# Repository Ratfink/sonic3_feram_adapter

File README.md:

# sonic3_feram_adapter
Breakout/adapter board for replacing the FeRAM chip in a Sonic 3 cartridge with
a modern chip.

## Licensing
Copyright © 2016 Clayton G. Hobbs.

This work is licensed under the Creative Commons Attribution-ShareAlike 4.0
International License. To view a copy of this license, visit
http://creativecommons.org/licenses/by-sa/4.0/ or send a letter to Creative
Commons, PO Box 1866, Mountain View, CA 94042, USA.

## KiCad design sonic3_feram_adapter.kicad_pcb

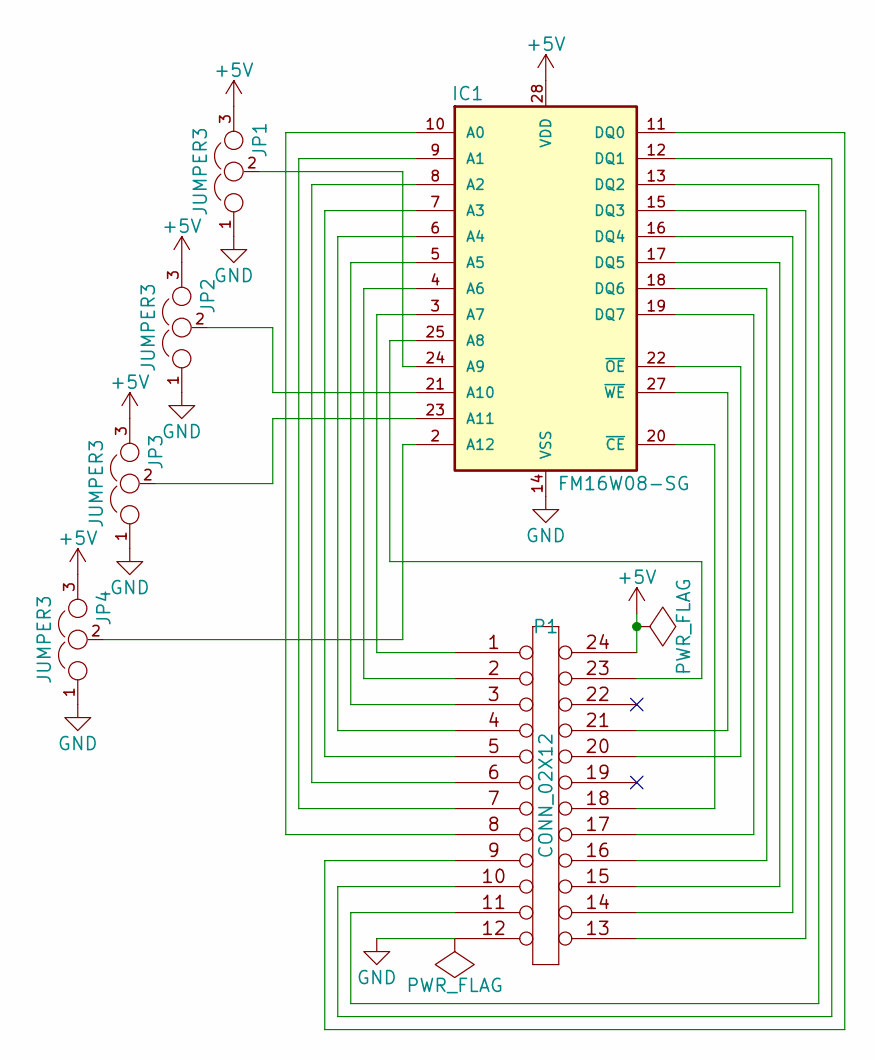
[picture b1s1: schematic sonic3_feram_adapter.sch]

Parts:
IC1: FM16W08-SG; SOIC-28_7.5x17.9mm_Pitch1.27mm
JP1, JP2, JP3, JP4: JUMPER3; SOLDER-JUMPER_2-WAY
P1: CONN_02X12; DIP-24_W15.24mm

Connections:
+5V: IC1.28 (VDD), JP1.3, JP2.3, JP3.3, JP4.3, P1.24
GND: IC1.14 (VSS), JP1.1, JP2.1, JP3.1, JP4.1, P1.12
unnamed: IC1.2 (A12), JP4.2
unnamed: IC1.3 (A7), P1.1
unnamed: IC1.4 (A6), P1.2
unnamed: IC1.5 (A5), P1.3
unnamed: IC1.6 (A4), P1.4
unnamed: IC1.7 (A3), P1.5
unnamed: IC1.8 (A2), P1.6
unnamed: IC1.9 (A1), P1.7
unnamed: IC1.10 (A0), P1.8
unnamed: IC1.11 (DQ0), P1.9
unnamed: IC1.12 (DQ1), P1.10
unnamed: IC1.13 (DQ2), P1.11
unnamed: IC1.15 (DQ3), P1.13
unnamed: IC1.16 (DQ4), P1.14
unnamed: IC1.17 (DQ5), P1.15
unnamed: IC1.18 (DQ6), P1.16
unnamed: IC1.19 (DQ7), P1.17
unnamed: IC1.20 (~CE~), P1.18
unnamed: IC1.21 (A10), JP2.2
unnamed: IC1.22 (~OE~), P1.20
unnamed: IC1.23 (A11), JP3.2
unnamed: IC1.24 (A9), JP1.2
unnamed: IC1.25 (A8), P1.23
unnamed: IC1.27 (~WE~), P1.21

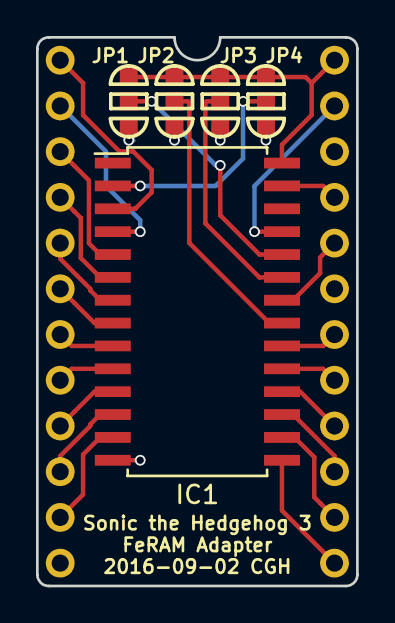
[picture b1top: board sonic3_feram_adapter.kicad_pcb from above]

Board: 2 copper layers, 17.8 x 30.5 mm, 6 parts (0 on the bottom side), 26 nets.

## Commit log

2016-09-02 Initial commit
    Added all the KiCAD files of the complete board, as well as a README and
    gitignore.
2016-09-02 Corrected PCB back text
    SMS is not Genesis, SMD is Genesis.
2016-09-16 Added jumpers for bank selection
    Since this board adapts an 8 KiB chip to work in the place of a 512 B
    chip, it seems like it would be nice to allow the user to change which
    block of 512 B is in use. To allow this, I added solder bump jumpers to
    the high address lines so they can be pulled to ground or 5 V.
2016-09-16 Improved footprint for header pins
    No more outline for an IC, and the designator is on the bottom of the
    board.
2016-09-16 Updated date on silkscreen
